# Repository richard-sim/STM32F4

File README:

OLIMEX STM32-E407 modified to fit under the 10x10cm PCB size limit that is common with PCB batch services such as Itead Studio and Seeed Studios.

- Moved the 3 BOOT headers inwards
- Rotated the BOOT UART port 180 to allow better trace placement
- Moved traces around the BOOT headers away from the PCB edge
- Moved the resistors on the BOOT pins to allow for the new placement of the headers

**NOTE** This has not been tested/verified/built yet!

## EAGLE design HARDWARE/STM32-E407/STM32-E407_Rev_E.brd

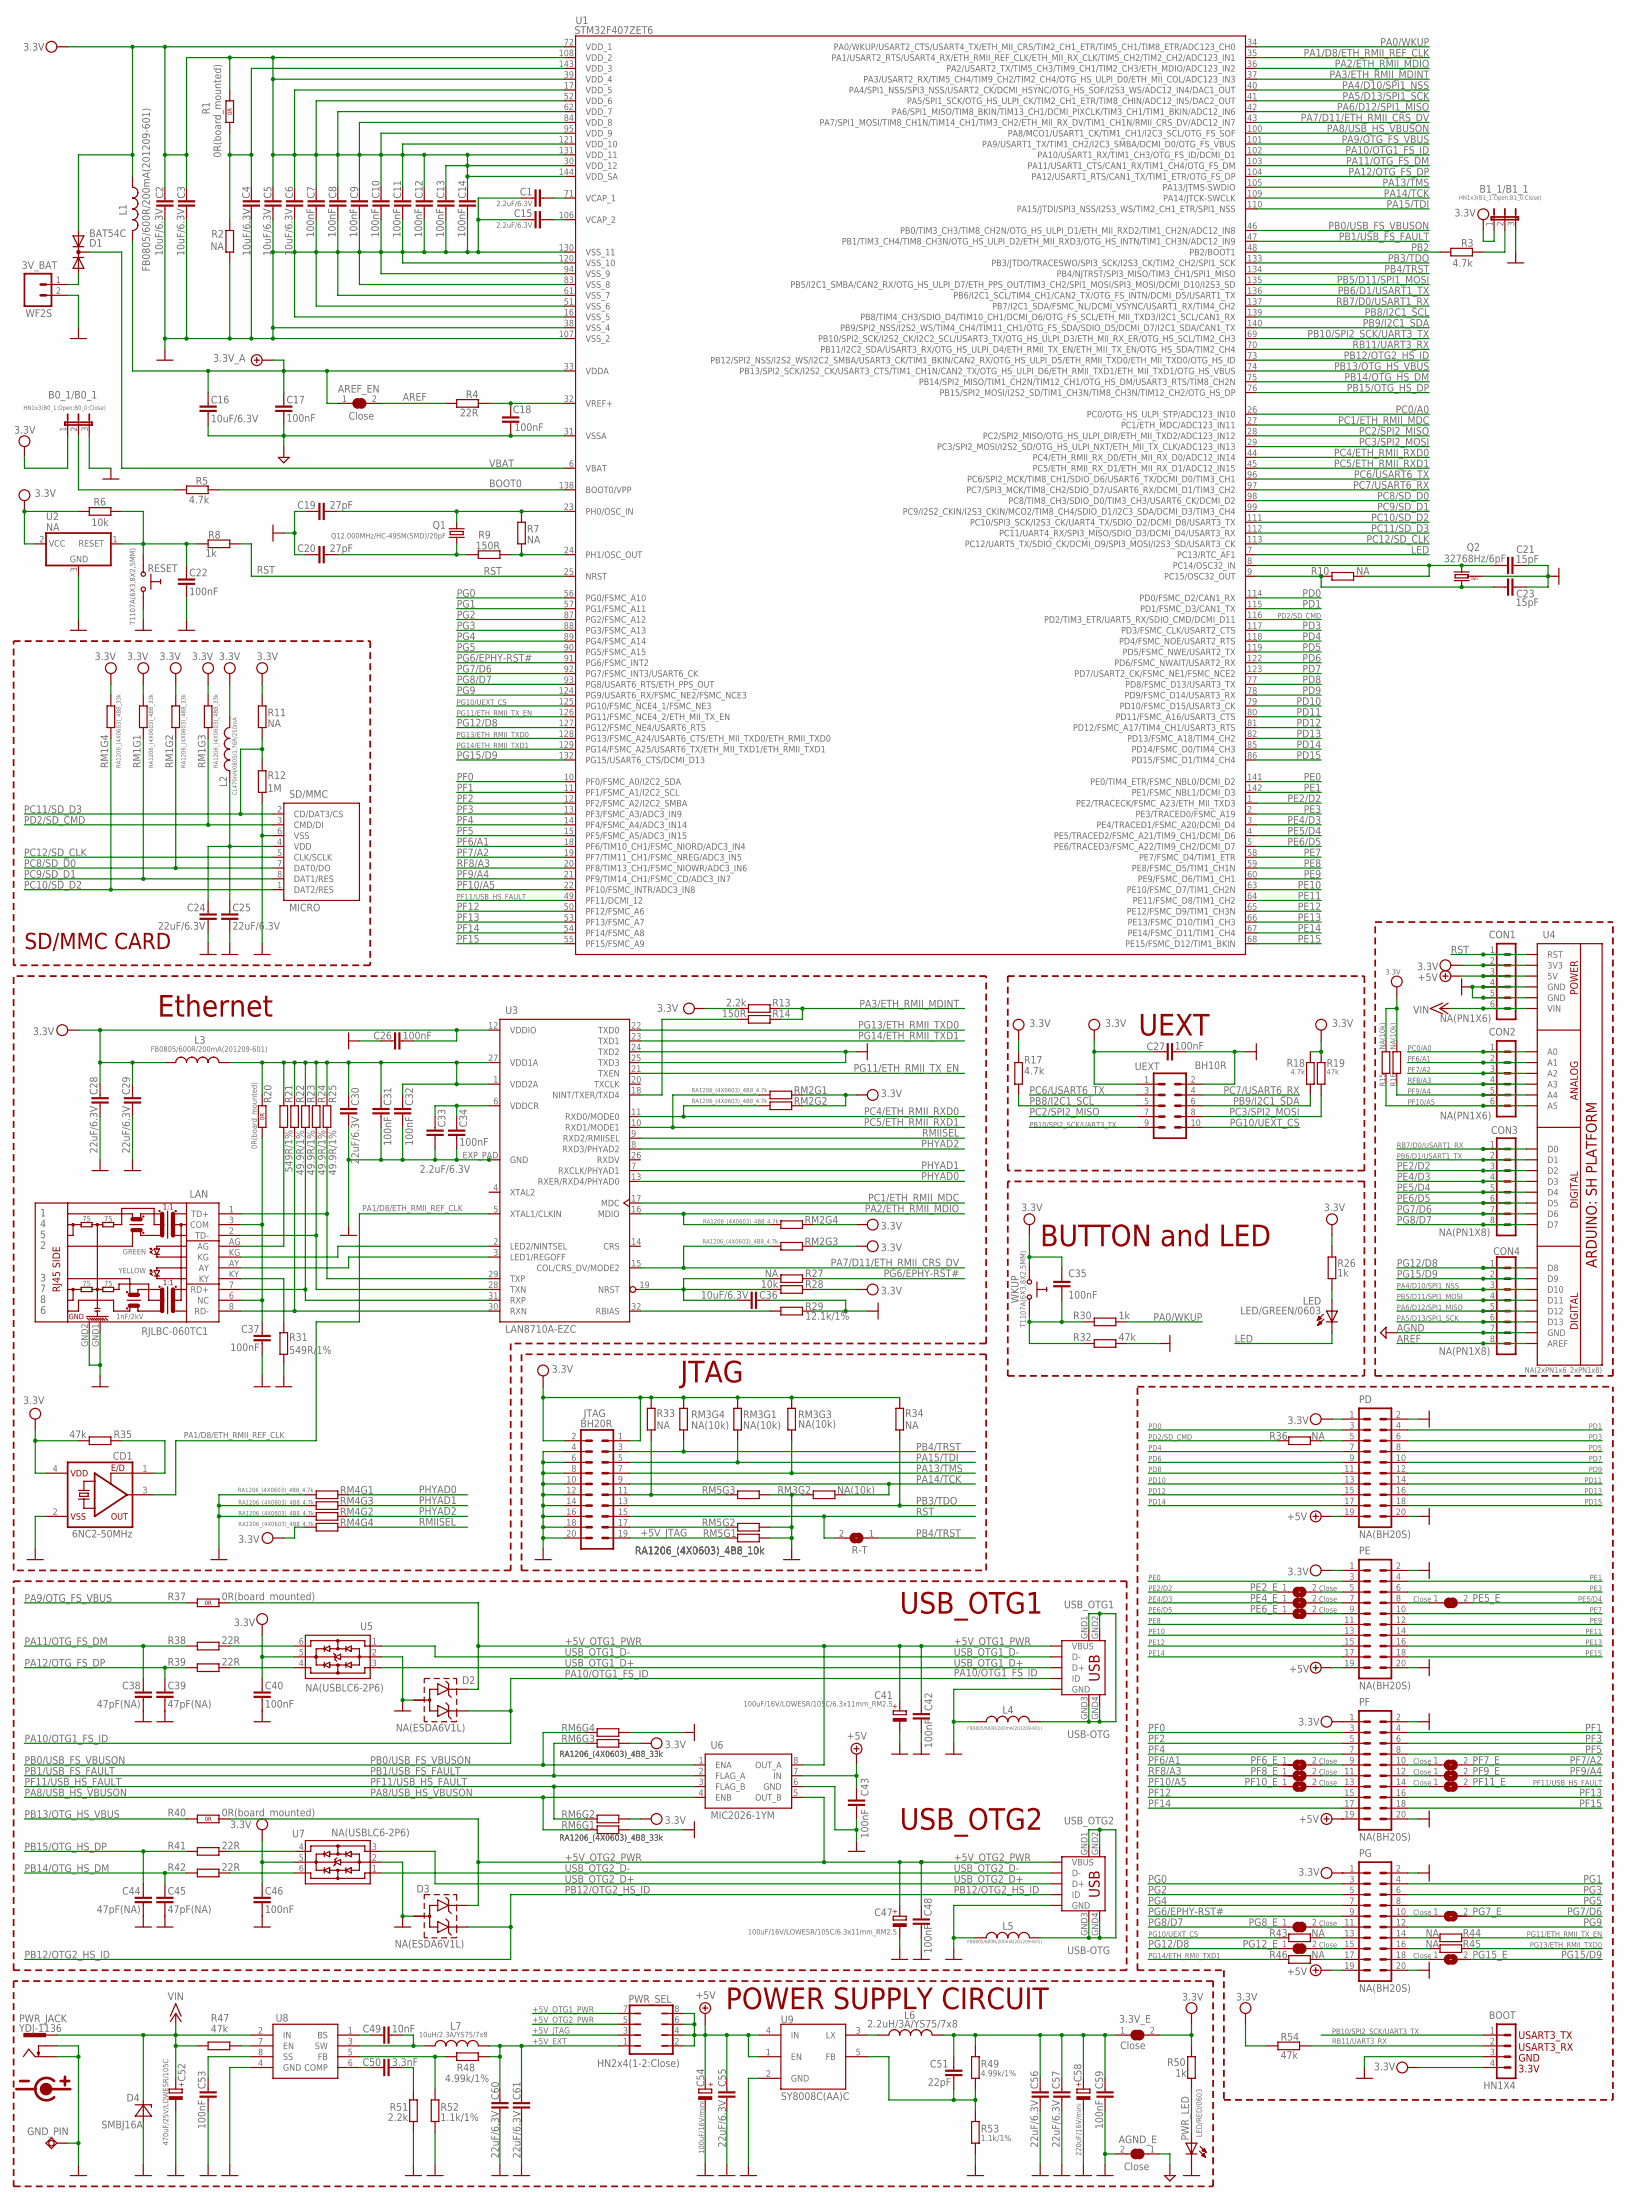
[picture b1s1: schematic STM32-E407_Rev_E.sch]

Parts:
3.3V_E: Close; SJ_1_SMALLER_CLOSE
3V_BAT: WF2S; CON2.54MM-2-0
AGND_E: Close; SJ_1_SMALLER_CLOSE
AREF_EN: Close; SJ_1_SMALLER_CLOSE
B0_1/B0_1: HN1x3(B0_1:Open;B0_0:Close); JP2
B1_1/B1_1: HN1x3(B1_1:Open;B1_0:Close); JP2
BOOT: HN1X4
C1, C15, C33: 2.2uF/6.3V; C0603_DWS
C2, C3, C4, C5, C6, C16, C36: 10uF/6.3V; C0603_DWS
C7, C8, C9, C10, C11, C12, C13, C14, C17, C18, C22, C26, C27, C31, C32, C34, C35, C37, C40, C42, C43, C46, C48, C53, C59: 100nF; C0603_DWS
C19, C20: 27pF; C0603_DWS
C21, C23: 15pF; C0603_DWS
C24, C25, C28, C29, C30, C55, C56, C57, C60, C61: 22uF/6.3V; C0603_DWS
C38, C39, C44, C45: 47pF(NA); C0603_DWS
C41, C47: 100uF/16V/LOWESR/105C/6.3x11mm_RM2.5; E2,5-6,3
C49: 10nF; C0603_DWS
C50: 3.3nF; C0603_DWS
C51: 22pF; C0603_DWS
C52: 470uF/25V/LOWESR/105C; E5-10,5
C54: 100uF/16V/mini; E2,5-6
C58: 220uF/16V/mini; E3,5-8
CD1: 6NC2-50MHz; 7X5MM_CLOCK_DRIVER
CON1, CON2: NA(PN1X6); PN1X6
CON3, CON4: NA(PN1X8); PN1X8
D1: BAT54C; SOT23C
D2, D3: NA(ESDA6V1L); SOT-23
D4: SMBJ16A; DO214AA
GND_PIN: TESTPAD3; TEST_PAD40/70/SQUARE
JTAG: BH20R
L1, L3, L4, L5: FB0805/600R/200mA(201209-601); L0805_5MIL_DWS
L2: CL470nH/0805/1.76R/250mA; L0805_5MIL_DWS
L6: 2.2uH/3A/YS75/7x8; L7078
L7: 10uH/2.3A/YS75/7x8; L7078
LAN: RJLBC-060TC1
LED: LED/GREEN/0603; LED-0603
PD: NA(BH20S); ML20-MALE
PE: NA(BH20S); ML20-MALE
PE2_E, PE4_E, PE5_E, PE6_E: Close; SJ_1_SMALLER_CLOSE
PF: NA(BH20S); ML20-MALE
PF6_E, PF7_E, PF8_E, PF9_E, PF10_E, PF11_E: Close; SJ_1_SMALLER_CLOSE
PG: NA(BH20S); ML20-MALE
PG7_E, PG8_E, PG12_E, PG15_E: Close; SJ_1_SMALLER_CLOSE
PWR_JACK: YDJ-1136; PWR_JACK_UNI_MILLING
PWR_LED: LED/RED/0603; LED-0603
PWR_SEL: HN2x4(1-2:Close); JP4Q_2
Q1: Q12.000MHz/HC-49SM(SMD)/20pF; HC49/SMD2_THIN
Q2: 32768Hz/6pF; TC26H_3_REPAIR_SMD
R1, R20, R37, R40: 0R(board_mounted); 0603_0R
R2, R7, R10, R11, R27, R33, R34, R36, R43, R44, R45, R46: NA; R0603_5MIL_DWS
R3, R5, R17, R18: 4.7k; R0603_5MIL_DWS
R4, R38, R39, R41, R42: 22R; R0603_5MIL_DWS
R6, R28: 10k; R0603_5MIL_DWS
R8, R26, R30, R50: 1k; R0603_5MIL_DWS
R9, R14: 150R; R0603_5MIL_DWS
R12: 1M; R0603_5MIL_DWS
R13, R51: 2.2k; R0603_5MIL_DWS
R15, R16: NA(10k); R0603_5MIL_DWS
R19, R32, R35, R47, R54: 47k; R0603_5MIL_DWS
R21, R31: 549R/1%; R0603_5MIL_DWS
R22, R23, R24, R25: 49.9R/1%; R0603_5MIL_DWS
R29: 12.1k/1%; R0603_5MIL_DWS
R48, R49: 4.99k/1%; R0603_5MIL_DWS
R52, R53: 1.1k/1%; R0603_5MIL_DWS
R-T: Open; SJ_1_SMALLER
RESET: T1107A(6X3,8X2,5MM); WS-TAKT_6X3.5_SMD_NOCREAM
RM1, RM6: RA1206_(4X0603)_4B8_33k; R_MATRIX_4
RM2, RM4: RA1206_(4X0603)_4B8_4.7k; R_MATRIX_4
RM3: NA(10k); R_MATRIX_4
RM5: RA1206_(4X0603)_4B8_10k; R_MATRIX_4
SD/MMC: MICRO; TFR/C-MEM-CON
U1: STM32F407ZET6; LQFP144
U2: NA; SOT23
U3: LAN8710A-EZC; QFN-32(DRILLS)
U4: NA(2xPN1x6_2xPN1x8); ARDUINO_SHIELD_PLATFORM_WITHOUT_DIMENSION
U5, U7: NA(USBLC6-2P6); USBLC6-2P6
U6: MIC2026-1YM; SO-8
U8: MP1482DS; SOIC8
U9: SY8008C(AA)C; SOT23-5
UEXT: BH10R
USB_OTG1, USB_OTG2: USB-OTG; USB_MINI_9PIN
WKUP: T1107A(6X3,8X2,5MM); WS-TAKT_6X3.5_SMD_NOCREAM

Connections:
+5V: C43.1, C54.+, C55.1, CON1.3, PD.19, PE.19, PF.19, PG.19, PWR_SEL.2, PWR_SEL.4, PWR_SEL.6, PWR_SEL.8, U4.5V, U6.7 (IN), U9.1 (EN), U9.4 (IN)
+5V_EXT: C60.1, C61.1, L7.2, PWR_SEL.1, R48.2
+5V_JTAG: JTAG.19, PWR_SEL.3, RM5.1.1 (1)
+5V_OTG1_PWR: C41.+, C42.1, D2.1, PWR_SEL.7, R37.2 (1.2), U6.8 (OUT_A), USB_OTG1.VBUS
+5V_OTG2_PWR: C47.+, C48.1, D3.1, PWR_SEL.5, R40.2 (1.2), U6.5 (OUT_B), USB_OTG2.VBUS
+7V: AREF_EN.1, C16.1, C17.2, L1.2, U1.33 (VDDA)
+15V: C52.+, CON1.6, D4.C, PWR_JACK.+, R47.1, U4.VIN, U8.2 (IN)
AGND: AGND_E.1, C16.2, C17.1, C18.1, CON4.7, U1.31 (VSSA), U4.GND@2 (GND)
AREF: AREF_EN.2, CON4.8, R4.1, U4.AREF
BOOT0: R5.1, U1.138 (BOOT0/VPP)
GND: 3V_BAT.2, AGND_E.2, B0_1/B0_1.3, B1_1/B1_1.3, BOOT.3, C1.1, C2.1, C3.1, C4.1, C5.1, C6.1, C7.1, C8.1, C9.1, C10.1, C11.1, C12.1, C13.1, C14.1, C15.1, C19.2, C20.2, C21.2, C22.1, C23.2, C24.2, C25.2, C26.1, C27.1, C28.1, C29.1, C30.1, C31.1, C32.1, C33.1, C34.1, C36.1, C37.1, C38.2, C39.2, C40.1, C41.-, C42.2, C43.2, C44.2, C45.2, C46.1, C47.-, C48.2, C52.-, C53.2, C54.-, C55.2, C56.2, C57.2, C58.-, C59.2, C60.2, C61.2, CD1.2 (VSS), CON1.4, CON1.5, D2.3, D3.3, D4.A, GND_PIN.P$1, JTAG.4, JTAG.6, JTAG.8, JTAG.10, JTAG.12, JTAG.14, JTAG.16, JTAG.18, JTAG.20, L4.1, L5.1, LAN.GND1, LAN.GND2, PD.2, PD.20, PE.2, PE.20, PF.2, PF.20, PG.2, PG.20, PWR_JACK.-, PWR_JACK.--, PWR_LED.C, Q2.GND, R2.2, R12.2, R29.1, R31.2, R32.1, R51.2, R52.2, R53.2, RESET.P$2 (1), RM3.2.1 (1), RM4.1.2 (2), RM4.2.2 (2), RM4.3.2 (2), RM5.1.2 (2), RM5.2.2 (2), RM5.3.2 (2), RM6.1.2 (2), RM6.4.2 (2), SD/MMC.6 (VSS), U1.16 (VSS_5), U1.38 (VSS_4), U1.51 (VSS_6), U1.61 (VSS_7), U1.83 (VSS_8), U1.94 (VSS_9), U1.107 (VSS_2), U1.120 (VSS_10), U1.130 (VSS_11), U2.3 (GND), U3.24 (TXD2), U3.25 (TXD3), U3.EP1 (GND1), U3.EP2 (GND2), U3.EP3 (GND3), U3.EP4 (GND4), U3.EP5 (GND5), U3.EP6 (GND6), U3.EP7 (GND7), U3.EP8 (GND8), U3.EP9 (GND9), U3.EXP_PAD (GND), U4.GND, U4.GND@1 (GND), U5.2, U6.6 (GND), U7.2, U8.4 (GND), U9.2 (GND), UEXT.2, USB_OTG1.GND, USB_OTG2.GND
LED: LED.C, U1.7 (PC13/RTC_AF1)
unnamed: C19.1, Q1.2, R7.2, U1.23 (PH0/OSC_IN)
unnamed: C20.1, Q1.1, R9.1
unnamed: R7.1, R9.2, U1.24 (PH1/OSC_OUT)
unnamed: JTAG.17, RM5.2.1 (1)
unnamed: LED.A, R26.1
unnamed: PD.5, R36.1
unnamed: C51.2, R49.2, R53.1, U9.5 (FB)
unnamed: B0_1/B0_1.2, R5.2
unnamed: 3.3V_E.1, C51.1, C56.1, C57.1, C58.+, C59.1, L6.2, R49.1
unnamed: PG.14, R44.2
unnamed: PF.13, PF10_E.2
unnamed: PG.16, R45.2
unnamed: PF.9, PF6_E.2
unnamed: PF.11, PF8_E.2
unnamed: PF.10, PF7_E.1
unnamed: PG.17, R46.1
unnamed: PF.12, PF9_E.1
unnamed: PG.10, PG7_E.1
unnamed: C35.1, R30.1, R32.2, WKUP.P$2 (1)
unnamed: PE.8, PE5_E.1
unnamed: PE.9, PE6_E.2
unnamed: PE.7, PE4_E.2
unnamed: B1_1/B1_1.2, R3.2
unnamed: PE.5, PE2_E.2
unnamed: C36.2, R27.2, R28.2, U3.19 (NRST)
unnamed: PG.11, PG8_E.2
unnamed: PG.15, PG12_E.2
unnamed: PG.18, PG15_E.1
unnamed: C53.1, U8.8 (SS)
unnamed: R47.2, U8.7 (EN)
unnamed: PG.13, R43.1
unnamed: PF.14, PF11_E.1
unnamed: LAN.1 (TD+), R25.1, U3.29 (TXP)
unnamed: LAN.2 (TD-), R24.1, U3.28 (TXN)
unnamed: R41.2, U7.4
unnamed: LAN.7 (RD+), R23.1, U3.31 (RXP)
unnamed: C49.1, U8.1 (BS)
unnamed: R42.2, U7.6
unnamed: LAN.8 (RD-), R22.1, U3.30 (RXN)
unnamed: C49.2, L7.1, U8.3 (SW)
unnamed: R38.2, U5.6
unnamed: R39.2, U5.4
unnamed: LAN.KG, U3.2 (LED2/NINTSEL)
unnamed: LAN.AY, U3.3 (LED1/REGOFF)
unnamed: R29.2, U3.32 (RBIAS)
unnamed: C37.2, LAN.3 (COM), LAN.6 (NC), R20.1 (1.1)
unnamed: LAN.KY, R31.1
unnamed: C33.2, C34.2, U3.6 (VDDCR)
unnamed: C30.2, C31.2, C32.2, L3.1, R20.2 (1.2), R21.1, R22.2, R23.2, R24.2, R25.2, U3.1 (VDD2A), U3.27 (VDD1A)
unnamed: C50.1, U8.6 (COMP)
unnamed: C50.2, R51.1
unnamed: R48.1, R52.1, U8.5 (FB)
unnamed: R14.2, U3.18 (NINT/TXER/TXD4)
unnamed: L6.1, U9.3 (LX)
unnamed: LAN.AG, R21.2
unnamed: 3V_BAT.1, D1.2 (A2)
unnamed: C24.1, C25.1, L2.2, SD/MMC.4 (VDD)
unnamed: JTAG.11, R33.1, RM5.3.1 (1)
unnamed: C1.2, U1.71 (VCAP_1)
unnamed: CD1.1 (E/D), R35.2
unnamed: C15.2, U1.106 (VCAP_2)
unnamed: PWR_LED.A, R50.2
unnamed: C22.2, R6.1, R8.2, RESET.P$1 (0), U2.1 (RESET)
unnamed: C4.2, R1.1 (1.1), R2.1, U1.143 (VDD_3)
PA0/WKUP: R30.2, U1.34 (PA0/WKUP/USART2_CTS/USART4_TX/ETH_MII_C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)
PA1/D8/ETH_RMII_REF_CLK: CD1.3 (OUT), U1.35 (PA1/USART2_RTS/USART4_RX/ETH_RMII_REF_C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), U3.5 (XTAL1/CLKIN)
PA2/ETH_RMII_MDIO: RM2.4.2 (2), U1.36 (PA2/USART2_TX/TIM5_CH3/TIM9_CH1/TIM2_CH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), U3.16 (MDIO)
PA3/ETH_RMII_MDINT: R13.1, R14.1, U1.37 (PA3/USART2_RX/TIM5_CH4/TIM9_CH2/TIM2_CH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)
PA4/D10/SPI1_NSS: CON4.3, U1.40 (PA4/SPI1_NSS/SPI3_NSS/USART2_CK/DCMI_HS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), U4.D10
PA5/D13/SPI1_SCK: CON4.6, U1.41 (PA5/SPI1_SCK/OTG_HS_ULPI_CK/TIM2_CH1_ET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), U4.D13
PA6/D12/SPI1_MISO: CON4.5, U1.42 (PA6/SPI1_MISO/TIM8_BKIN/TIM13_CH1/DCMI_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), U4.D12
PA7/D11/ETH_RMII_CRS_DV: RM2.3.2 (2), U1.43 (PA7/SPI1_MOSI/TIM8_CH1N/TIM14_CH1/TIM3_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), U3.15 (COL/CRS_DV/MODE2)
PA8/USB_HS_VBUSON: RM6.1.1 (1), U1.100 (PA8/MCO1/USART1_CK/TIM1_CH1/I2C3_SCL/OT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), U6.4 (ENB)
PA9/OTG_FS_VBUS: R37.1 (1.1), U1.101 (PA9/USART1_TX/TIM1_CH2/I2C3_SMBA/DCMI_D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)
PA10/OTG1_FS_ID: D2.2, U1.102 (PA10/USART1_RX/TIM1_CH3/OTG_FS_ID/DCMI_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), USB_OTG1.ID
PA11/OTG_FS_DM: C38.1, R38.1, U1.103 (PA11/USART1_CTS/CAN1_RX/TIM1_CH4/OTG_FS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)
PA12/OTG_FS_DP: C39.1, R39.1, U1.104 (PA12/USART1_RTS/CAN1_TX/TIM1_ETR/OTG_FS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)
PA13/TMS: JTAG.7, RM3.3.1 (1), U1.105 (PA13/JTMS-SWDIO)
PA14/TCK: JTAG.9, RM3.2.2 (2), U1.109 (PA14/JTCK-SWCLK)
PA15/TDI: JTAG.5, RM3.1.1 (1), U1.110 (PA15/JTDI/SPI3_NSS/I2S3_WS/TIM2_CH1_ETR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)
PB0/USB_FS_VBUSON: RM6.4.1 (1), U1.46 (PB0/TIM3_CH3/TIM8_CH2N/OTG_HS_ULPI_D1/E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), U6.1 (ENA)
PB1/USB_FS_FAULT: RM6.3.1 (1), U1.47 (PB1/TIM3_CH4/TIM8_CH3N/OTG_HS_ULPI_D2/E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), U6.2 (FLAG_A)
PB2: R3.1, U1.48 (PB2/BOOT1)
PB3/TDO: JTAG.13, R34.1, U1.133 (PB3/JTDO/TRACESWO/SPI3_SCK/I2S3_CK/TIM2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)
PB4/TRST: JTAG.3, R-T.1, RM3.4.1 (1), U1.134 (PB4/NJTRST/SPI3_MISO/TIM3_CH1/SPI1_MISO)
PB5/D11/SPI1_MOSI: CON4.4, U1.135 (PB5/I2C1_SMBA/CAN2_RX/OTG_HS_ULPI_D7/ET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), U4.D11
PB6/D1/USART1_TX: CON3.2, U1.136 (PB6/I2C1_SCL/TIM4_CH1/CAN2_TX/OTG_FS_IN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), U4.D1
PB8/I2C1_SCL: R17.1, U1.139 (PB8/TIM4_CH3/SDIO_D4/TIM10_CH1/DCMI_D6/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), UEXT.5
PB9/I2C1_SDA: R18.1, U1.140 (PB9/SPI2_NSS/I2S2_WS/TIM4_CH4/TIM11_CH1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), UEXT.6
PB10/SPI2_SCK/UART3_TX: BOOT.1, U1.69 (PB10/SPI2_SCK/I2S2_CK/I2C2_SCL/USART3_T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), UEXT.9
PB12/OTG2_HS_ID: D3.2, U1.73 (PB12/SPI2_NSS/I2S2_WS/I2C2_SMBA/USART3_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), USB_OTG2.ID
PB13/OTG_HS_VBUS: R40.1 (1.1), U1.74 (PB13/SPI2_SCK/I2S2_CK/USART3_CTS/TIM1_C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)
PB14/OTG_HS_DM: C45.1, R42.1, U1.75 (PB14/SPI2_MISO/TIM1_CH2N/TIM12_CH1/OTG_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)
PB15/OTG_HS_DP: C44.1, R41.1, U1.76 (PB15/SPI2_MOSI/I2S2_SD/TIM1_CH3N/TIM8_C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)
PC0/A0: CON2.1, U1.26 (PC0/OTG_HS_ULPI_STP/ADC123_IN10), U4.A0
PC1/ETH_RMII_MDC: U1.27 (PC1/ETH_MDC/ADC123_IN11), U3.17 (MDC)
PC2/SPI2_MISO: U1.28 (PC2/SPI2_MISO/OTG_HS_ULPI_DIR/ETH_MII_T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), UEXT.7
PC3/SPI2_MOSI: R19.1, U1.29 (PC3/SPI2_MOSI/I2S2_SD/OTG_HS_ULPI_NXT/E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), UEXT.8
PC4/ETH_RMII_RXD0: RM2.2.2 (2), U1.44 (PC4/ETH_RMII_RX_D0/ETH_MII_RX_D0/ADC12_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), U3.11 (RXD0/MODE0)
PC5/ETH_RMII_RXD1: RM2.1.2 (2), U1.45 (PC5/ETH_RMII_RX_D1/ETH_MII_RX_D1/ADC12_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), U3.10 (RXD1/MODE1)
PC6/USART6_TX: U1.96 (PC6/SPI2_MCK/TIM8_CH1/SDIO_D6/USART6_TX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), UEXT.3
PC7/USART6_RX: U1.97 (PC7/SPI3_MCK/TIM8_CH2/SDIO_D7/USART6_RX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), UEXT.4
PC8/SD_D0: RM1.2.1 (1), SD/MMC.7 (DAT0/DO), U1.98 (PC8/TIM8_CH3/SDIO_D0/TIM3_CH3/USART6_CK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)
PC9/SD_D1: RM1.1.1 (1), SD/MMC.8 (DAT1/RES), U1.99 (PC9/I2S2_CKIN/I2S3_CKIN/MCO2/TIM8_CH4/S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)
PC10/SD_D2: RM1.4.1 (1), SD/MMC.1 (DAT2/RES), U1.111 (PC10/SPI3_SCK/I2S3_CK/UART4_TX/SDIO_D2/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)
PC11/SD_D3: R11.2, R12.1, SD/MMC.2 (CD/DAT3/CS), U1.112 (PC11/UART4_RX/SPI3_MISO/SDIO_D3/DCMI_D4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)
PC12/SD_CLK: SD/MMC.5 (CLK/SCLK), U1.113 (PC12/UART5_TX/SDIO_CK/DCMI_D9/SPI3_MOSI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)
PC14: C21.1, Q2.2, R10.2, U1.8 (PC14/OSC32_IN)
PC15: C23.1, Q2.1, R10.1, U1.9 (PC15/OSC32_OUT)
PD0: PD.3, U1.114 (PD0/FSMC_D2/CAN1_RX)
PD1: PD.4, U1.115 (PD1/FSMC_D3/CAN1_TX)
PD2/SD_CMD: R36.2, RM1.3.1 (1), SD/MMC.3 (CMD/DI), U1.116 (PD2/TIM3_ETR/UART5_RX/SDIO_CMD/DCMI_D11)
PD3: PD.6, U1.117 (PD3/FSMC_CLK/USART2_CTS)
PD4: PD.7, U1.118 (PD4/FSMC_NOE/USART2_RTS)
PD5: PD.8, U1.119 (PD5/FSMC_NWE/USART2_TX)
PD6: PD.9, U1.122 (PD6/FSMC_NWAIT/USART2_RX)
PD7: PD.10, U1.123 (PD7/USART2_CK/FSMC_NE1/FSMC_NCE2)
PD8: PD.11, U1.77 (PD8/FSMC_D13/USART3_TX)
PD9: PD.12, U1.78 (PD9/FSMC_D14/USART3_RX)
PD10: PD.13, U1.79 (PD10/FSMC_D15/USART3_CK)
PD11: PD.14, U1.80 (PD11/FSMC_A16/USART3_CTS)
PD12: PD.15, U1.81 (PD12/FSMC_A17/TIM4_CH1/USART3_RTS)
PD13: PD.16, U1.82 (PD13/FSMC_A18/TIM4_CH2)
PD14: PD.17, U1.85 (PD14/FSMC_D0/TIM4_CH3)
PD15: PD.18, U1.86 (PD15/FSMC_D1/TIM4_CH4)
PE0: PE.3, U1.141 (PE0/TIM4_ETR/FSMC_NBL0/DCMI_D2)
PE1: PE.4, U1.142 (PE1/FSMC_NBL1/DCMI_D3)
PE2/D2: CON3.3, PE2_E.1, U1.1 (PE2/TRACECK/FSMC_A23/ETH_MII_TXD3), U4.D2
PE3: PE.6, U1.2 (PE3/TRACED0/FSMC_A19)
PE4/D3: CON3.4, PE4_E.1, U1.3 (PE4/TRACED1/FSMC_A20/DCMI_D4), U4.D3
PE5/D4: CON3.5, PE5_E.2, U1.4 (PE5/TRACED2/FSMC_A21/TIM9_CH1/DCMI_D6), U4.D4
PE6/D5: CON3.6, PE6_E.1, U1.5 (PE6/TRACED3/FSMC_A22/TIM9_CH2/DCMI_D7), U4.D5
PE7: PE.10, U1.58 (PE7/FSMC_D4/TIM1_ETR)
PE8: PE.11, U1.59 (PE8/FSMC_D5/TIM1_CH1N)
PE9: PE.12, U1.60 (PE9/FSMC_D6/TIM1_CH1)
PE10: PE.13, U1.63 (PE10/FSMC_D7/TIM1_CH2N)
PE11: PE.14, U1.64 (PE11/FSMC_D8/TIM1_CH2)
PE12: PE.15, U1.65 (PE12/FSMC_D9/TIM1_CH3N)
PE13: PE.16, U1.66 (PE13/FSMC_D10/TIM1_CH3)
PE14: PE.17, U1.67 (PE14/FSMC_D11/TIM1_CH4)
PE15: PE.18, U1.68 (PE15/FSMC_D12/TIM1_BKIN)
PF0: PF.3, U1.10 (PF0/FSMC_A0/I2C2_SDA)
PF1: PF.4, U1.11 (PF1/FSMC_A1/I2C2_SCL)
PF2: PF.5, U1.12 (PF2/FSMC_A2/I2C2_SMBA)
PF3: PF.6, U1.13 (PF3/FSMC_A3/ADC3_IN9)
PF4: PF.7, U1.14 (PF4/FSMC_A4/ADC3_IN14)
PF5: PF.8, U1.15 (PF5/FSMC_A5/ADC3_IN15)
PF6/A1: CON2.2, PF6_E.1, U1.18 (PF6/TIM10_CH1/FSMC_NIORD/ADC3_IN4), U4.A1
PF7/A2: CON2.3, PF7_E.2, U1.19 (PF7/TIM11_CH1/FSMC_NREG/ADC3_IN5), U4.A2
PF9/A4: CON2.5, PF9_E.2, R16.1, U1.21 (PF9/TIM14_CH1/FSMC_CD/ADC3_IN7), U4.A4
PF10/A5: CON2.6, PF10_E.1, R15.1, U1.22 (PF10/FSMC_INTR/ADC3_IN8), U4.A5
PF11/USB_HS_FAULT: PF11_E.2, RM6.2.1 (1), U1.49 (PF11/DCMI_12), U6.3 (FLAG_B)
PF12: PF.15, U1.50 (PF12/FSMC_A6)
PF13: PF.16, U1.53 (PF13/FSMC_A7)
PF14: PF.17, U1.54 (PF14/FSMC_A8)
PF15: PF.18, U1.55 (PF15/FSMC_A9)
PG0: PG.3, U1.56 (PG0/FSMC_A10)
PG1: PG.4, U1.57 (PG1/FSMC_A11)
PG2: PG.5, U1.87 (PG2/FSMC_A12)
PG3: PG.6, U1.88 (PG3/FSMC_A13)
PG4: PG.7, U1.89 (PG4/FSMC_A14)
PG5: PG.8, U1.90 (PG5/FSMC_A15)
PG6/EPHY-RST#: PG.9, R27.1, U1.91 (PG6/FSMC_INT2)
PG7/D6: CON3.7, PG7_E.2, U1.92 (PG7/FSMC_INT3/USART6_CK), U4.D6
PG8/D7: CON3.8, PG8_E.1, U1.93 (PG8/USART6_RTS/ETH_PPS_OUT), U4.D7
PG9: PG.12, U1.124 (PG9/USART6_RX/FSMC_NE2/FSMC_NCE3)
PG10/UEXT_CS: R43.2, U1.125 (PG10/FSMC_NCE4_1/FSMC_NE3), UEXT.10
PG11/ETH_RMII_TX_EN: R44.1, U1.126 (PG11/FSMC_NCE4_2/ETH_MII_TX_EN), U3.21 (TXEN)
PG12/D8: CON4.1, PG12_E.1, U1.127 (PG12/FSMC_NE4/USART6_RTS), U4.D8
PG13/ETH_RMII_TXD0: R45.1, U1.128 (PG13/FSMC_A24/USART6_CTS/ETH_MII_TXD0/E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), U3.22 (TXD0)
PG14/ETH_RMII_TXD1: R46.2, U1.129 (PG14/FSMC_A25/USART6_TX/ETH_MII_TXD1/ET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), U3.23 (TXD1)
PG15/D9: CON4.2, PG15_E.2, U1.132 (PG15/USART6_CTS/DCMI_D13), U4.D9
PHYAD0: RM4.1.1 (1), U3.13 (RXER/RXD4/PHYAD0)
PHYAD1: RM4.3.1 (1), U3.7 (RXCLK/PHYAD1)
PHYAD2: RM4.2.1 (1), U3.8 (RXD3/PHYAD2)
RB7/D0/USART1_RX: CON3.1, U1.137 (PB7/I2C1_SDA/FSMC_NL/DCMI_VSYNC/USART1_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), U4.D0
RB11/UART3_RX: BOOT.2, R54.1, U1.70 (PB11/I2C2_SDA/USART3_RX/OTG_HS_ULPI_D4/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)
RF8/A3: CON2.4, PF8_E.1, U1.20 (PF8/TIM13_CH1/FSMC_NIOWR/ADC3_IN6), U4.A3
RMIISEL: RM4.4.1 (1), U3.9 (RXD2/RMIISEL)
RST: CON1.1, JTAG.15, R8.1, R-T.2, U1.25 (NRST), U4.RST
USB_OTG1_D+: U5.3, USB_OTG1.D+
USB_OTG1_D-: U5.1, USB_OTG1.D-
USB_OTG2_D+: U7.3, USB_OTG2.D+
USB_OTG2_D-: U7.1, USB_OTG2.D-
USB_SHIELD1: L5.2, USB_OTG2.GND1, USB_OTG2.GND2, USB_OTG2.GND3, USB_OTG2.GND4
USB_SHIELD2: L4.2, USB_OTG1.GND1, USB_OTG1.GND2, USB_OTG1.GND3, USB_OTG1.GND4
VBAT: D1.3 (K), U1.6 (VBAT)
VCC: 3.3V_E.2, B0_1/B0_1.1, B1_1/B1_1.1, BOOT.4, C2.2, C3.2, C5.2, C6.2, C7.2, C8.2, C9.2, C10.2, C11.2, C12.2, C13.2, C14.2, C26.2, C27.2, C28.2, C29.2, C35.2, C40.2, C46.2, CD1.4 (VDD), CON1.2, D1.1 (A1), JTAG.1, JTAG.2, L1.1, L2.1, L3.2, PD.1, PE.1, PF.1, PG.1, R1.2 (1.2), R6.2, R11.1, R13.2, R15.2, R16.2, R17.2, R18.2, R19.2, R26.2, R28.1, R33.2, R34.2, R35.1, R50.1, R54.2, RM1.1.2 (2), RM1.2.2 (2), RM1.3.2 (2), RM1.4.2 (2), RM2.1.1 (1), RM2.2.1 (1), RM2.3.1 (1), RM2.4.1 (1), RM3.1.2 (2), RM3.3.2 (2), RM3.4.2 (2), RM4.4.2 (2), RM6.2.2 (2), RM6.3.2 (2), U1.17 (VDD_5), U1.30 (VDD_12), U1.39 (VDD_4), U1.52 (VDD_6), U1.62 (VDD_7), U1.72 (VDD_1), U1.84 (VDD_8), U1.95 (VDD_9), U1.108 (VDD_2), U1.121 (VDD_10), U1.131 (VDD_11), U1.144 (VDD_SA), U2.2 (VCC), U3.12 (VDDIO), U4.3V3, U5.5, U7.5, UEXT.1, WKUP.P$1 (0)
VREF+: C18.2, R4.2, U1.32 (VREF+)

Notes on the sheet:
POWER SUPPLY CIRCUIT
BUTTON and LED
JTAG
SD/MMC CARD
USART3_TX
USART3_RX
GND
UEXT
USB_OTG1
USB_OTG2
3.3V
Ethernet

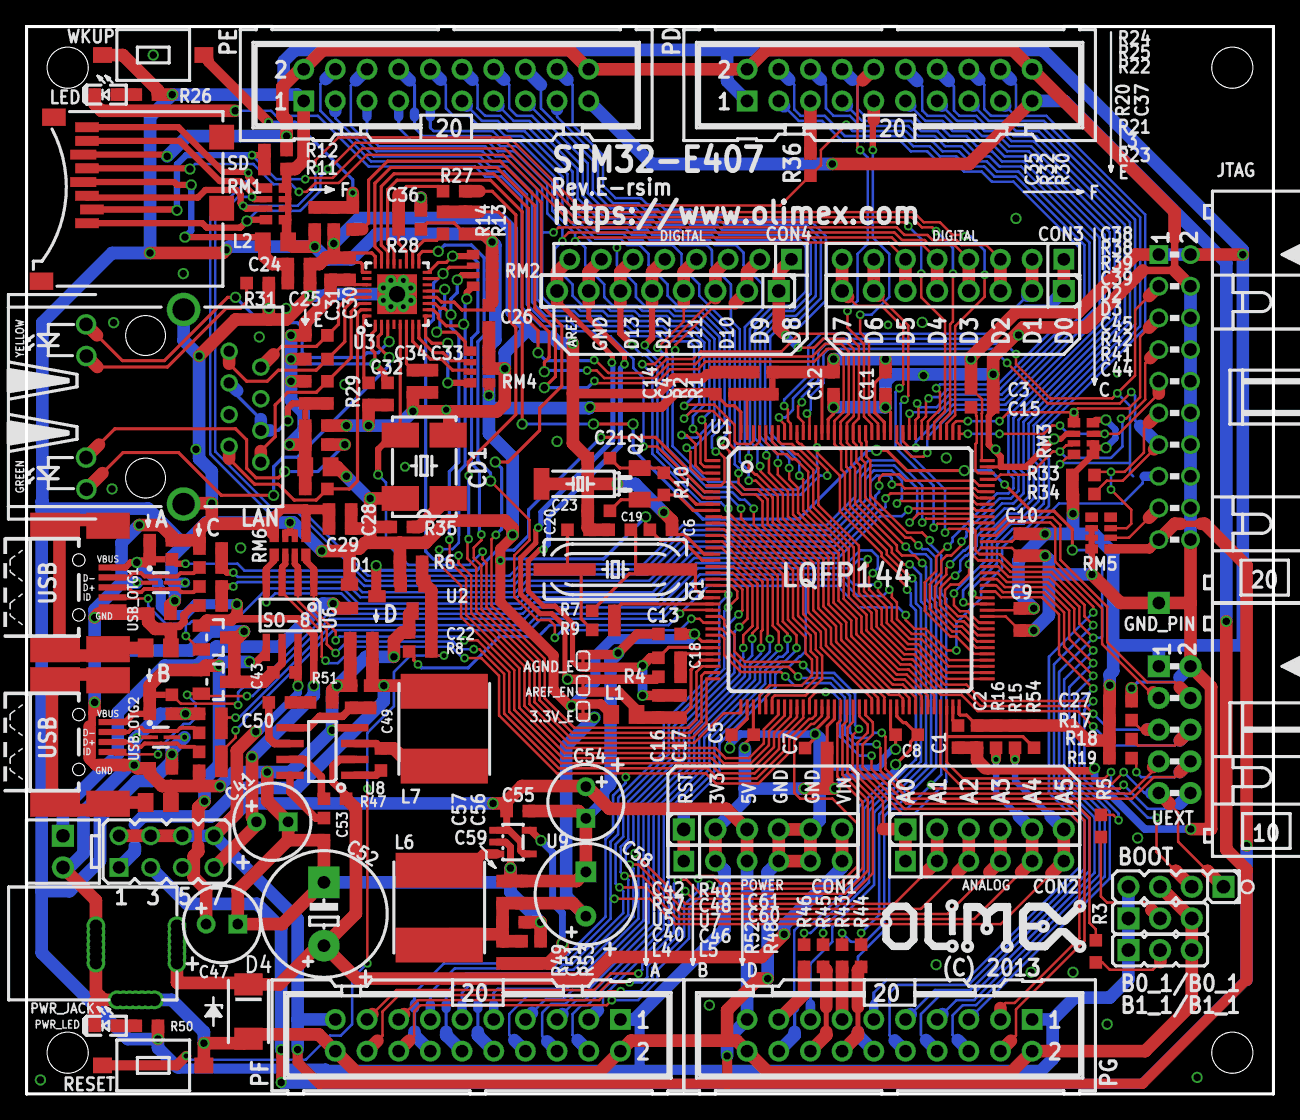
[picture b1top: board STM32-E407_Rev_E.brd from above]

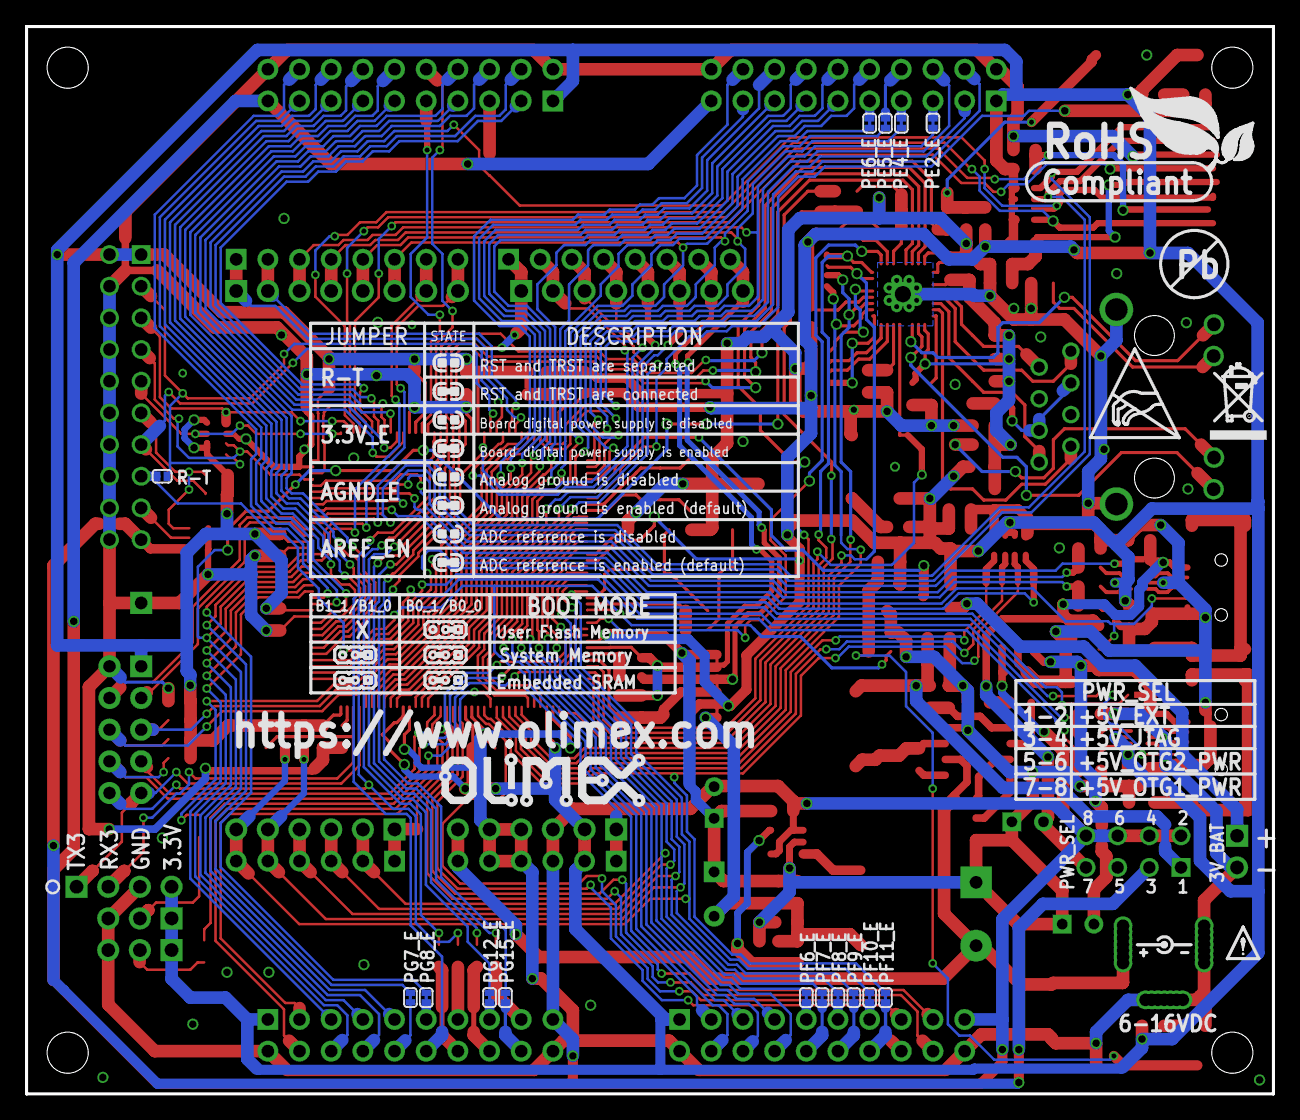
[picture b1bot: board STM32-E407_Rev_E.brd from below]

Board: 2 copper layers, 100.0 x 85.6 mm, 194 parts (21 on the bottom side), 201 nets.

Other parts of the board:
U$4, U$7: OLIMEX1_V
U$5: ESD_SYMBOL
U$6: PB
U$8: RECYCLE_BIN1/8
U$15: ROHS
U$16: ATTENTION_SMALL

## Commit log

2014-03-21 OLIMEX STM32-E407 modified to fit under the 10x10cm PCB size limit that is common with PCB batch services such as Itead Studio and Seeed Studios.
    - Moved the 3 BOOT headers inwards
    - Rotated the BOOT UART port 180 to allow better trace placement
    - Moved traces around the BOOT headers away from the PCB edge
    - Moved the resistors on the BOOT pins to allow for the new placement of the headers
2014-03-21 Added gerbers to make getting the PCB made easy!
2014-03-21 Added note to readme that the PCB has yet to be built/verified. Proceed with caution!
